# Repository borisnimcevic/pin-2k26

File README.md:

# pin-2k26

Design assets for the BalCCon 2k26 PCB-style pin/badge.

## Structure

- `svg/` — vector source files (Inkscape)
  - `pcb-only.svg` — final PCB-only artwork
  - `logo2k26_08.08-original.svg` — original full logo artwork
  - `pcb-assets.svg`, `pcb-decomposed.svg`, `date.svg` — decomposed/layered PCB artwork elements
- `png/colors/` — rendered color variants (black, blue, green, purple, red, white, yellow)
- `png/swatches/` — small reference color swatches (FR4 board color, grey)
- `balccon-2k26-hardware/` — KiCad project for the physical pin/badge PCB (schematic, board, routed and with silkscreen finished)
  - `pcb-svg/` — SVG layers exported from KiCad (`copper.svg`, `mask-front.svg`, `mask-back.svg`, `silkscreen-front.svg`, `esge-cuts.svg`, `hex.svg`, `log.svg`, `date.svg`)
  - `fabrication/` — Gerber and drill files exported for board fabrication

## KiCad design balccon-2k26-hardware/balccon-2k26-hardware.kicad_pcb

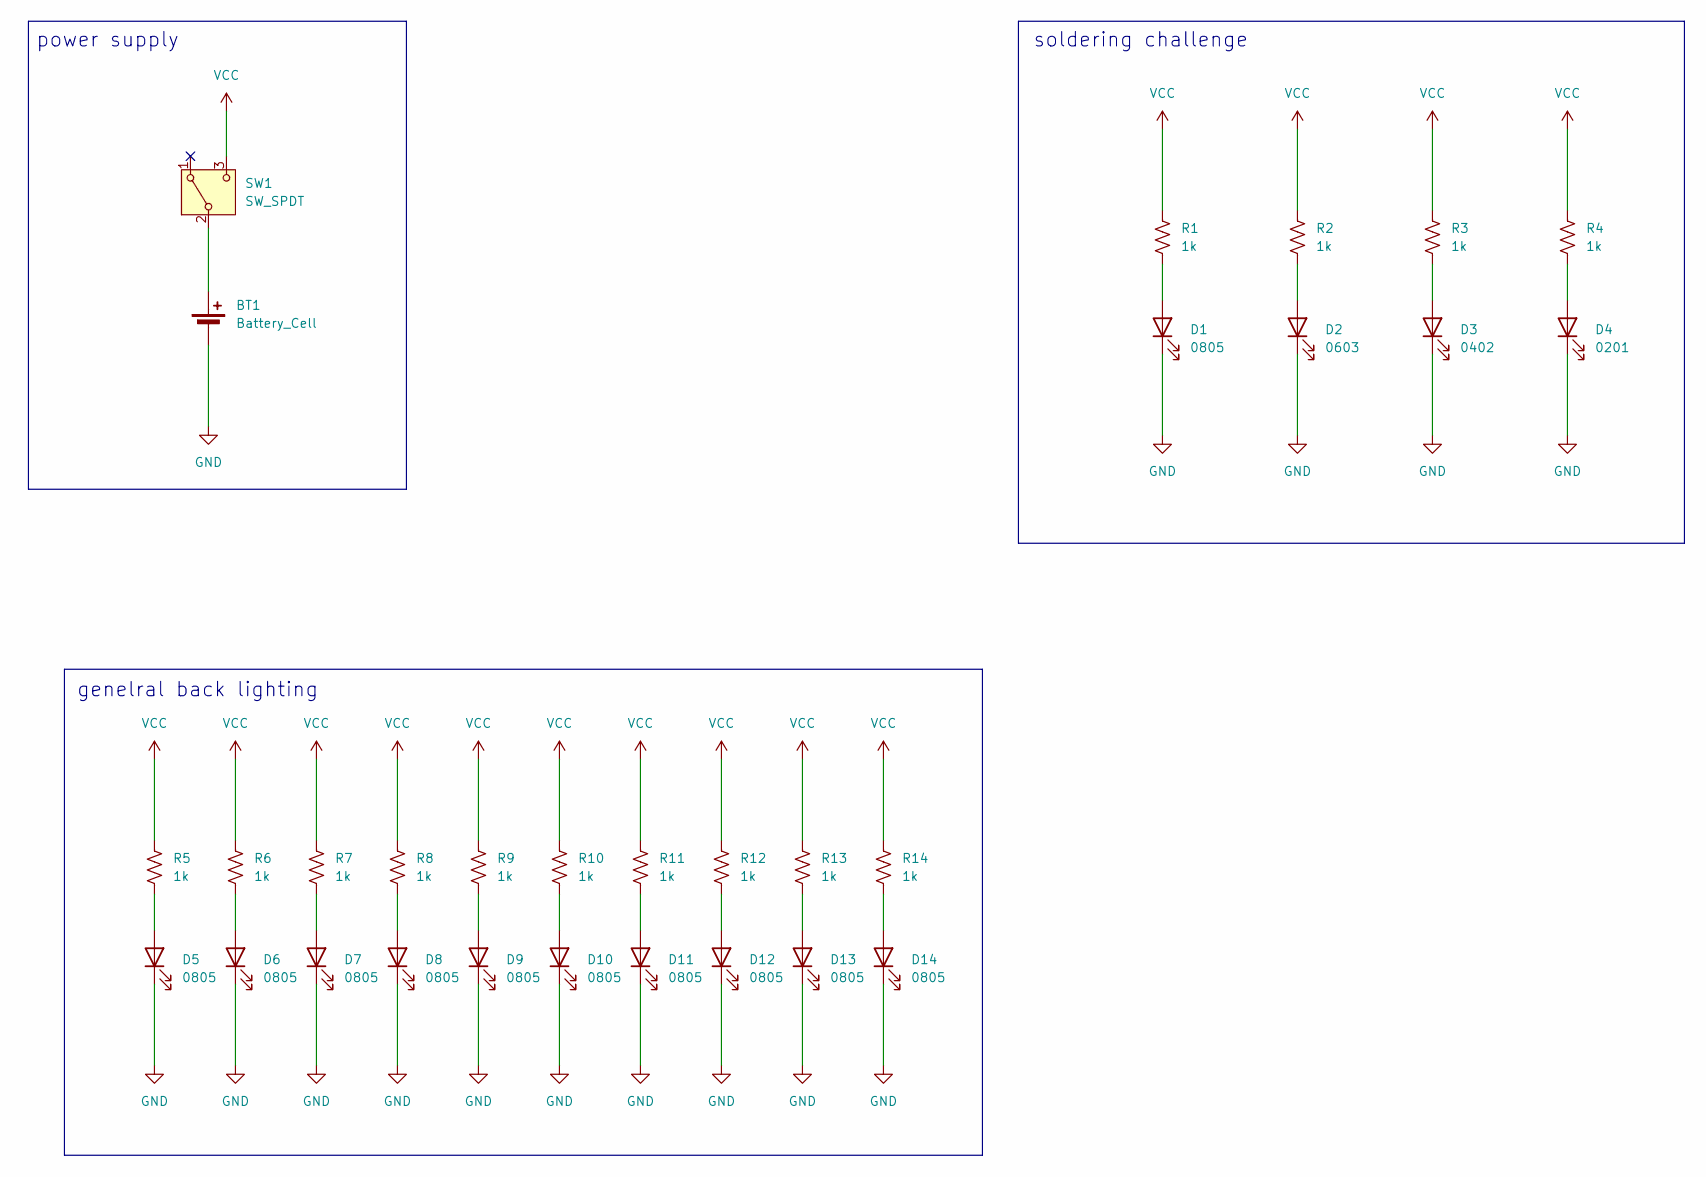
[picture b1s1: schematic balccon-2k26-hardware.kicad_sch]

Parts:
BT1: Battery_Cell; BatteryHolder_Keystone_3002_1x2032
D1, D5, D6, D7, D8, D9, D10, D11, D12, D13, D14: 0805; LED_0805_2012Metric_Pad1.15x1.40mm_HandSolder
D2: 0603; LED_0603_1608Metric_Pad1.05x0.95mm_HandSolder
D3: 0402; LED_0402_1005Metric_Pad0.77x0.64mm_HandSolder
D4: 0201; LED_0201_0603Metric_Pad0.64x0.40mm_HandSolder
R1, R2, R3, R4, R5, R6, R7, R8, R9, R10, R11, R12, R13, R14: 1k; R_0805_2012Metric_Pad1.20x1.40mm_HandSolder
SW1: SW_SPDT; SW_SPDT_PCM12

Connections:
GND: BT1.2 (-), D1.1 (K), D2.1 (K), D3.1 (K), D4.1 (K), D5.1 (K), D6.1 (K), D7.1 (K), D8.1 (K), D9.1 (K), D10.1 (K), D11.1 (K), D12.1 (K), D13.1 (K), D14.1 (K)
unnamed: BT1.1 (+), SW1.2 (B)
unnamed: D1.2 (A), R1.2
unnamed: D2.2 (A), R2.2
unnamed: D3.2 (A), R3.2
unnamed: D4.2 (A), R4.2
unnamed: D5.2 (A), R5.2
unnamed: D6.2 (A), R6.2
unnamed: D7.2 (A), R7.2
unnamed: D8.2 (A), R8.2
unnamed: D9.2 (A), R9.2
unnamed: D10.2 (A), R10.2
unnamed: D11.2 (A), R11.2
unnamed: D12.2 (A), R12.2
unnamed: D13.2 (A), R13.2
unnamed: D14.2 (A), R14.2
VCC: R1.1, R2.1, R3.1, R4.1, R5.1, R6.1, R7.1, R8.1, R9.1, R10.1, R11.1, R12.1, R13.1, R14.1, SW1.3 (C)

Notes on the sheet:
soldering challenge
genelral back lighting
power supply

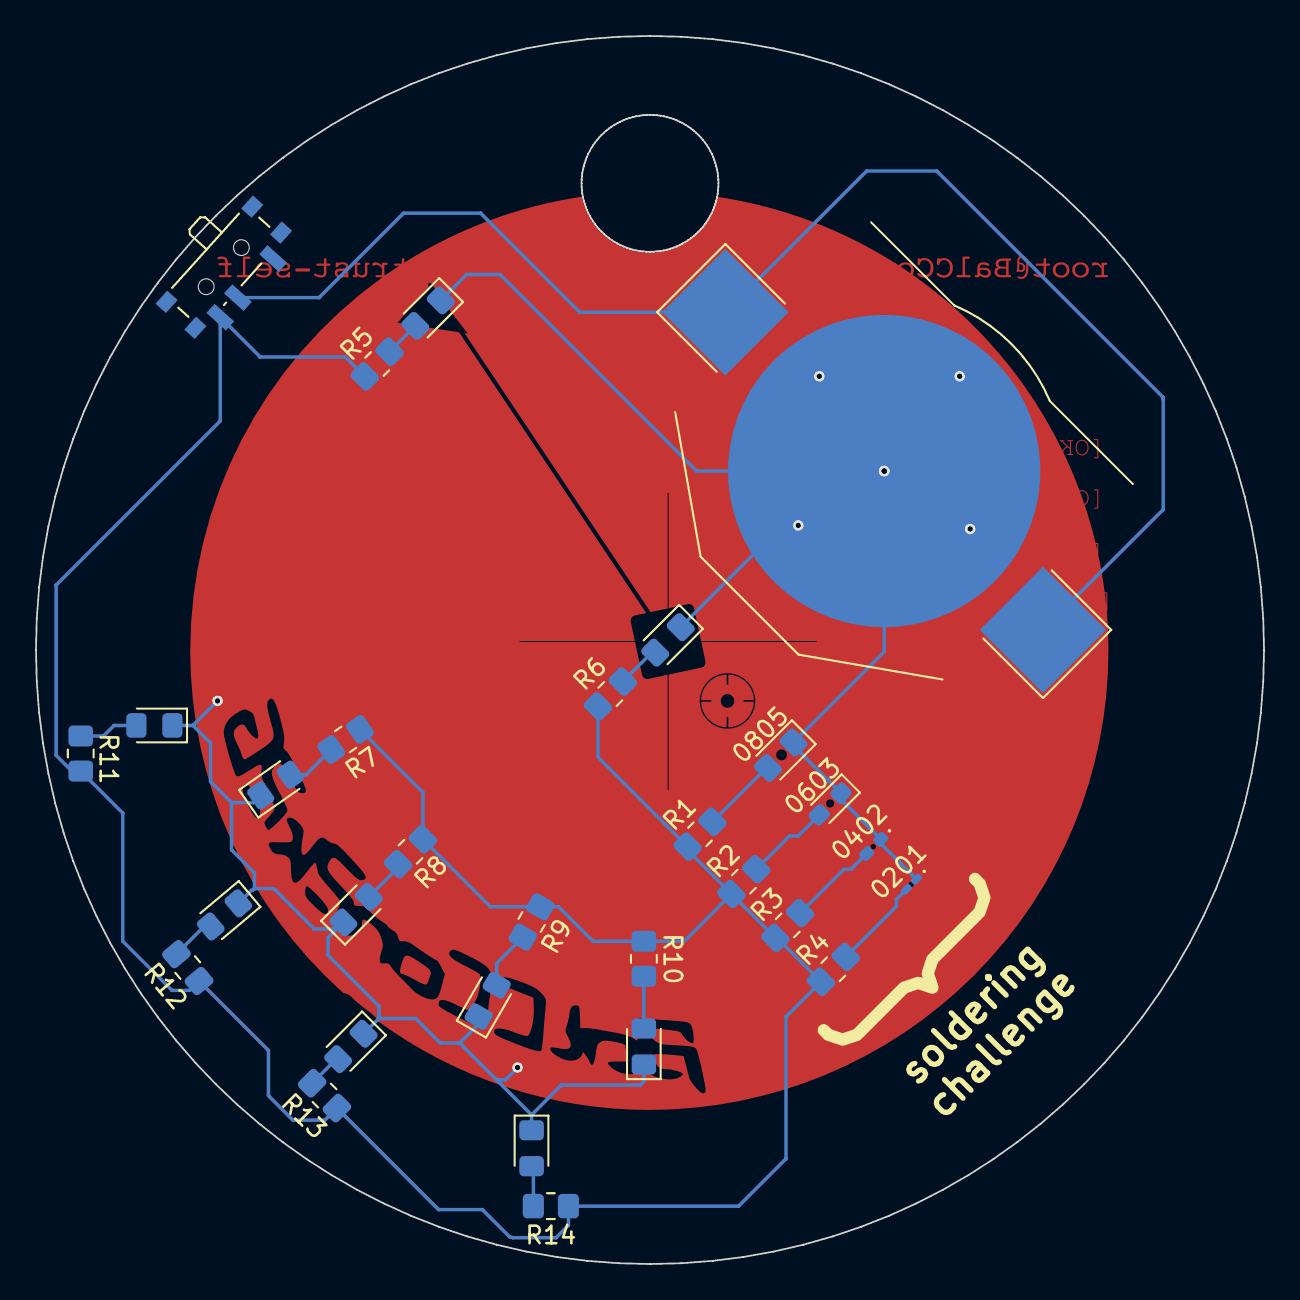
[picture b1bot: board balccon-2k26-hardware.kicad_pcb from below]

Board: 2 copper layers, 70.0 x 70.0 mm, 30 parts (30 on the bottom side), 17 nets.
